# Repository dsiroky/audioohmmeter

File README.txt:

http://www.smallbulb.net/audioohmmeter

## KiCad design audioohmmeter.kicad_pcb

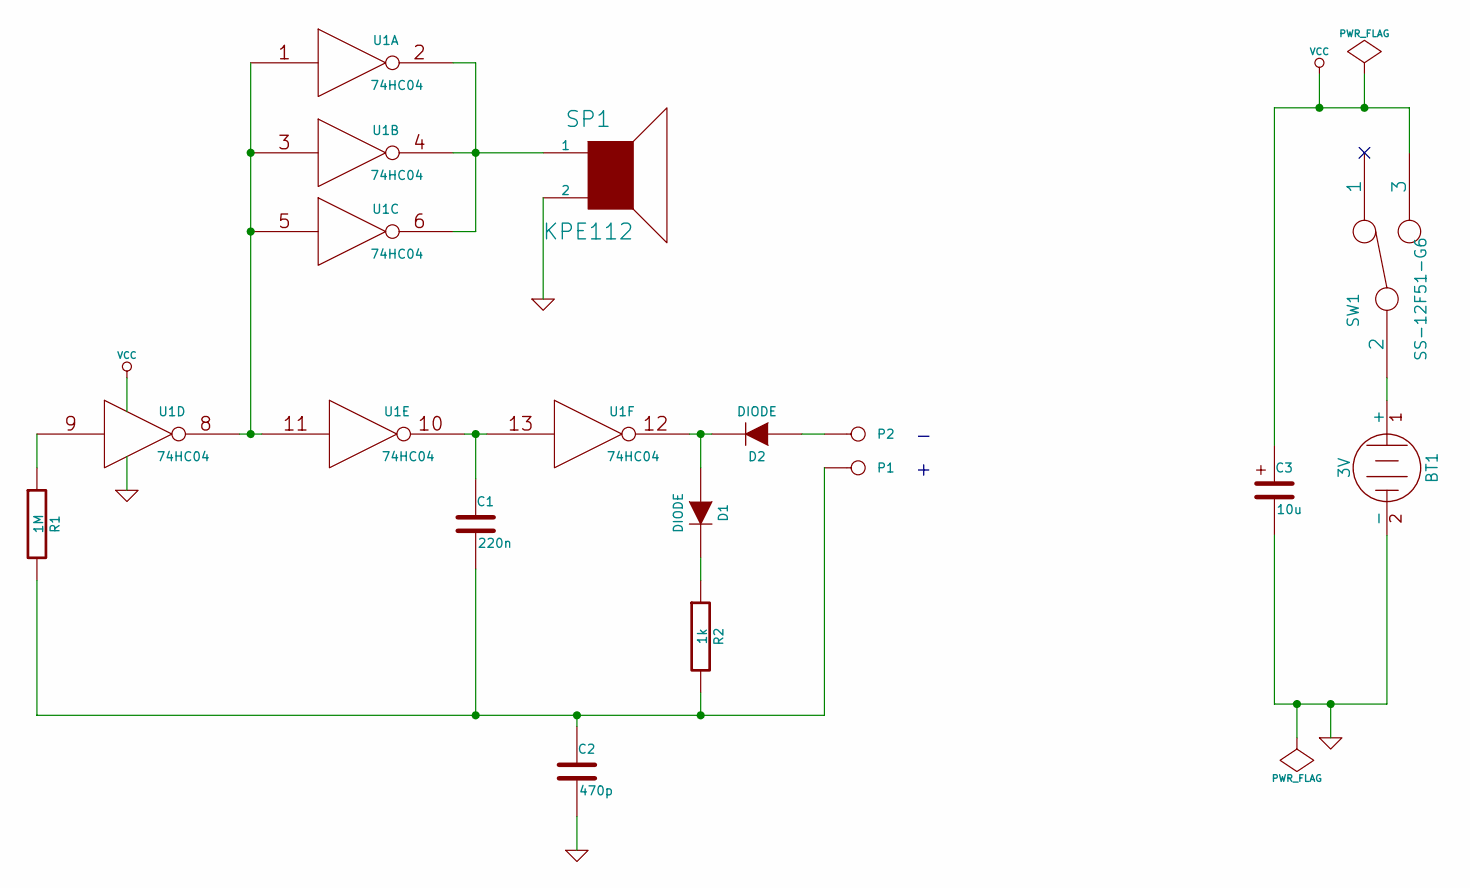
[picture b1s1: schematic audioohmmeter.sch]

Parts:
BT1: 3V
C1: 220n
C2: 470p
C3: 10u
D1, D2: DIODE
P1, P2: CONN_1
R1: 1M
R2: 1k
SP1: KPE112
SW1: SS-12F51-G6
U1: 74HC04

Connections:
GND: BT1.2 (-), C2.2, C3.2, SP1.2, U1.7 (GND)
unnamed: BT1.1 (+), SW1.2
unnamed: C1.1, U1.10, U1.13
unnamed: C1.2, C2.1, P1.1, R1.2, R2.2
unnamed: D1.1 (A), D2.2 (K), U1.12
unnamed: D1.2 (K), R2.1
unnamed: D2.1 (A), P2.1
unnamed: R1.1, U1.9
unnamed: SP1.1, U1.2, U1.4, U1.6
unnamed: U1.1, U1.3, U1.5, U1.8, U1.11
VCC: C3.1, SW1.3, U1.14 (VCC)

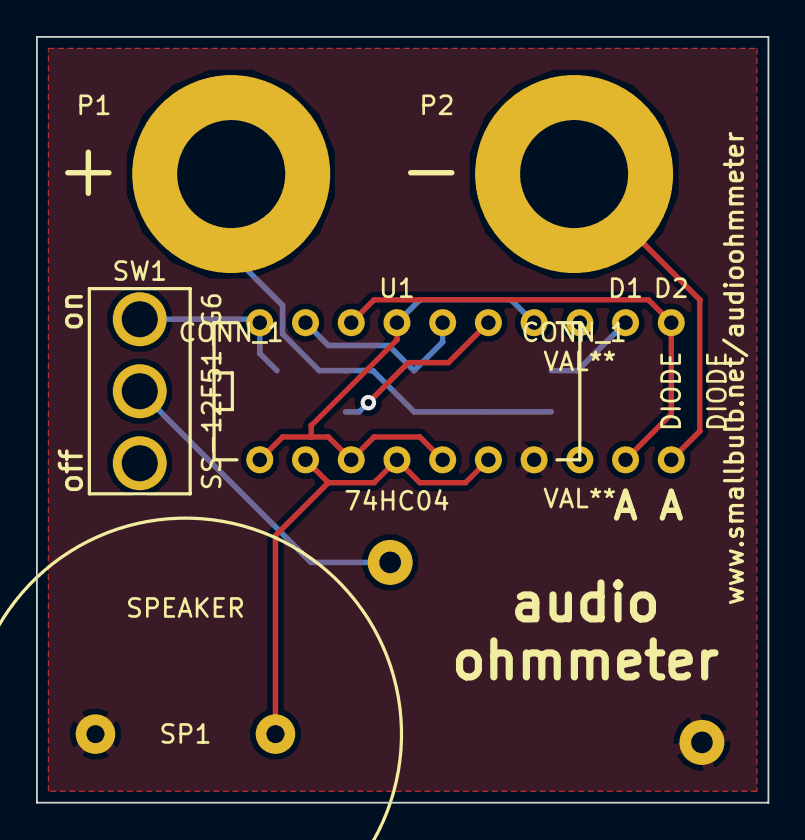
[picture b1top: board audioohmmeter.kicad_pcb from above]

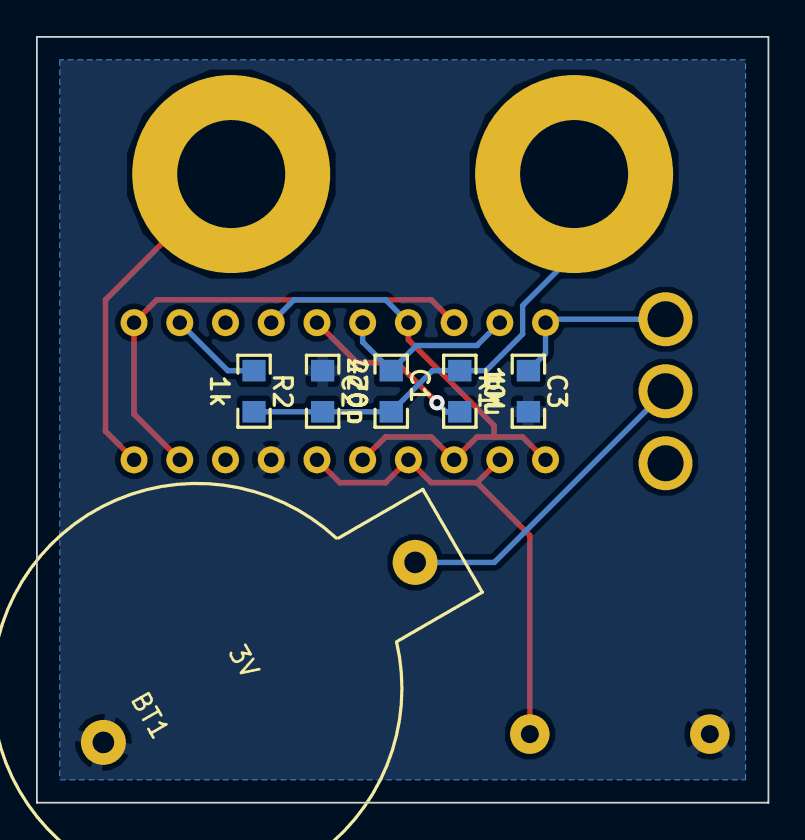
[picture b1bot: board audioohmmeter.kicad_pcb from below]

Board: 2 copper layers, 40.6 x 42.5 mm, 15 parts (6 on the bottom side), 11 nets.

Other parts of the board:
1pin, 1pin#2: VAL**; 1pin

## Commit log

2014-02-23 name fix, gerber files
2014-03-01 tweaks
